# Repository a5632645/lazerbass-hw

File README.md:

# half demo  
watch it on https://www.bilibili.com/video/BV1h2w5eRECL

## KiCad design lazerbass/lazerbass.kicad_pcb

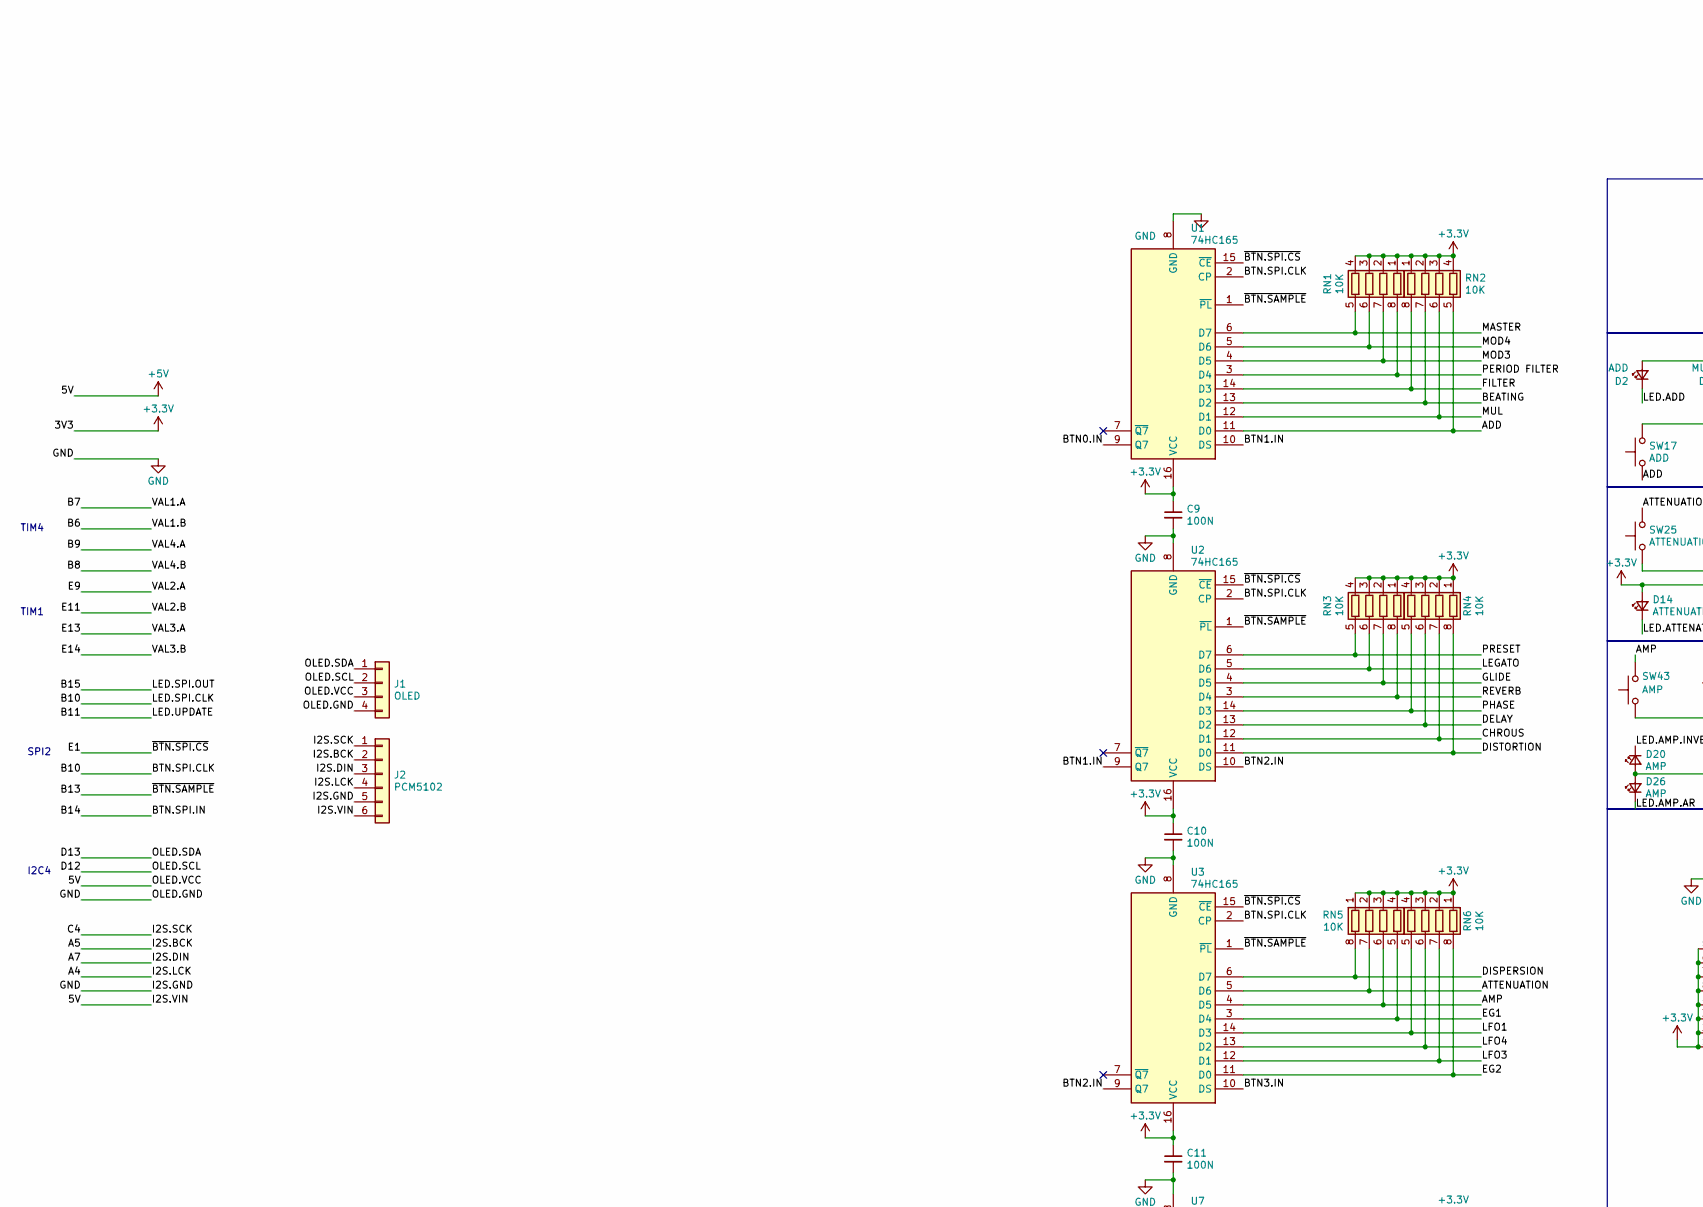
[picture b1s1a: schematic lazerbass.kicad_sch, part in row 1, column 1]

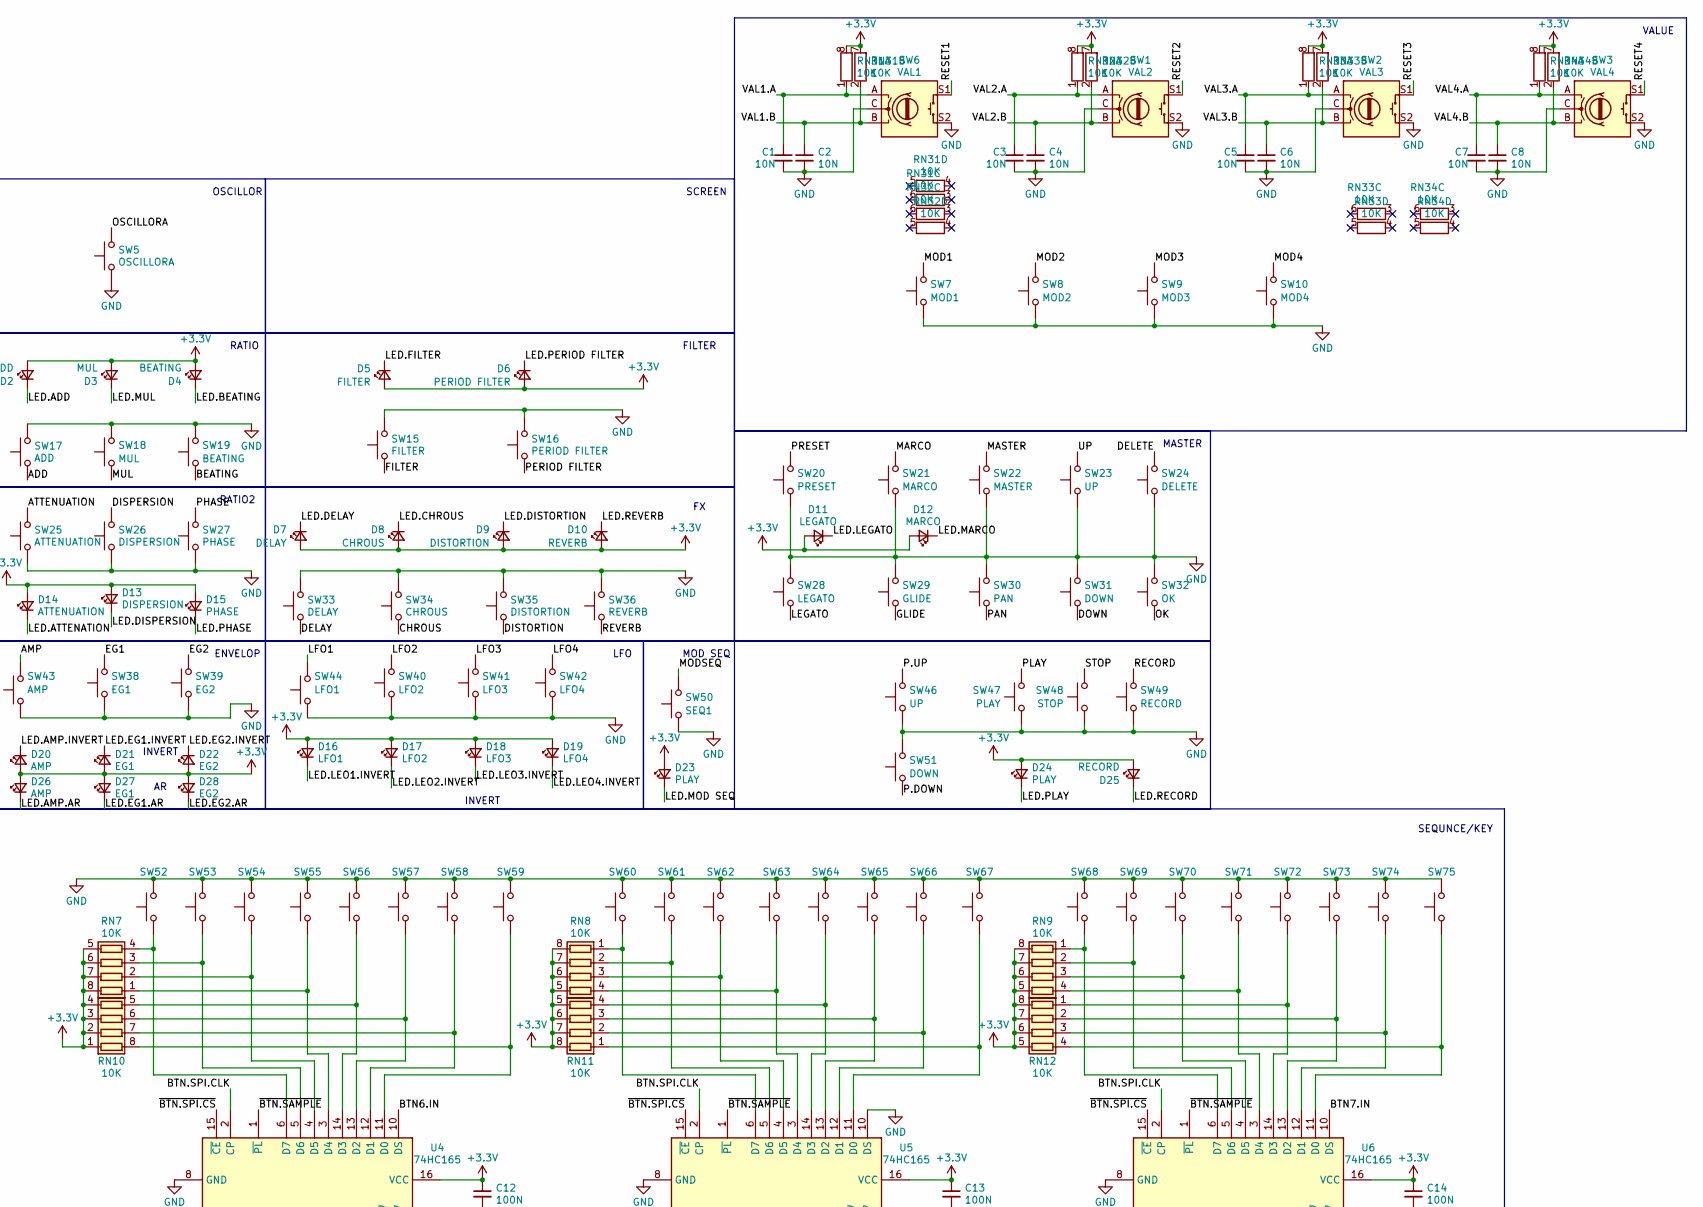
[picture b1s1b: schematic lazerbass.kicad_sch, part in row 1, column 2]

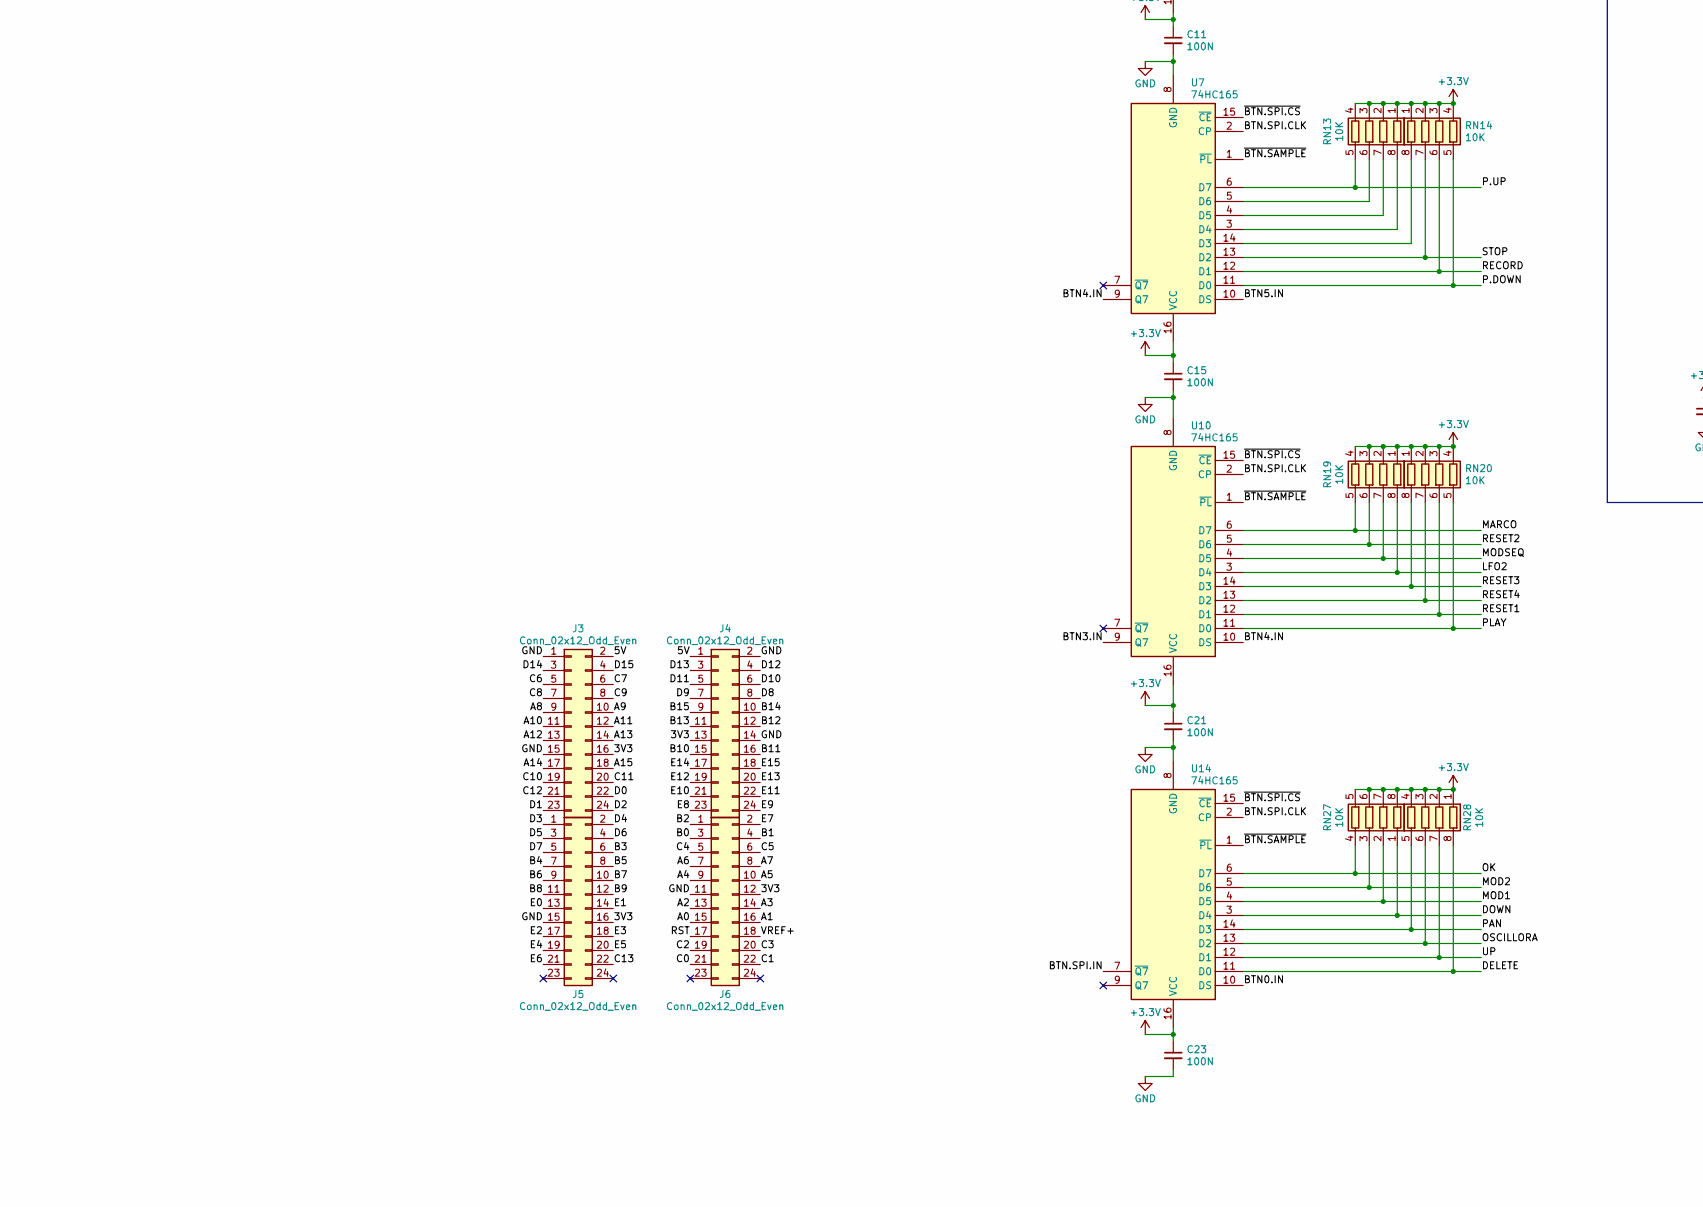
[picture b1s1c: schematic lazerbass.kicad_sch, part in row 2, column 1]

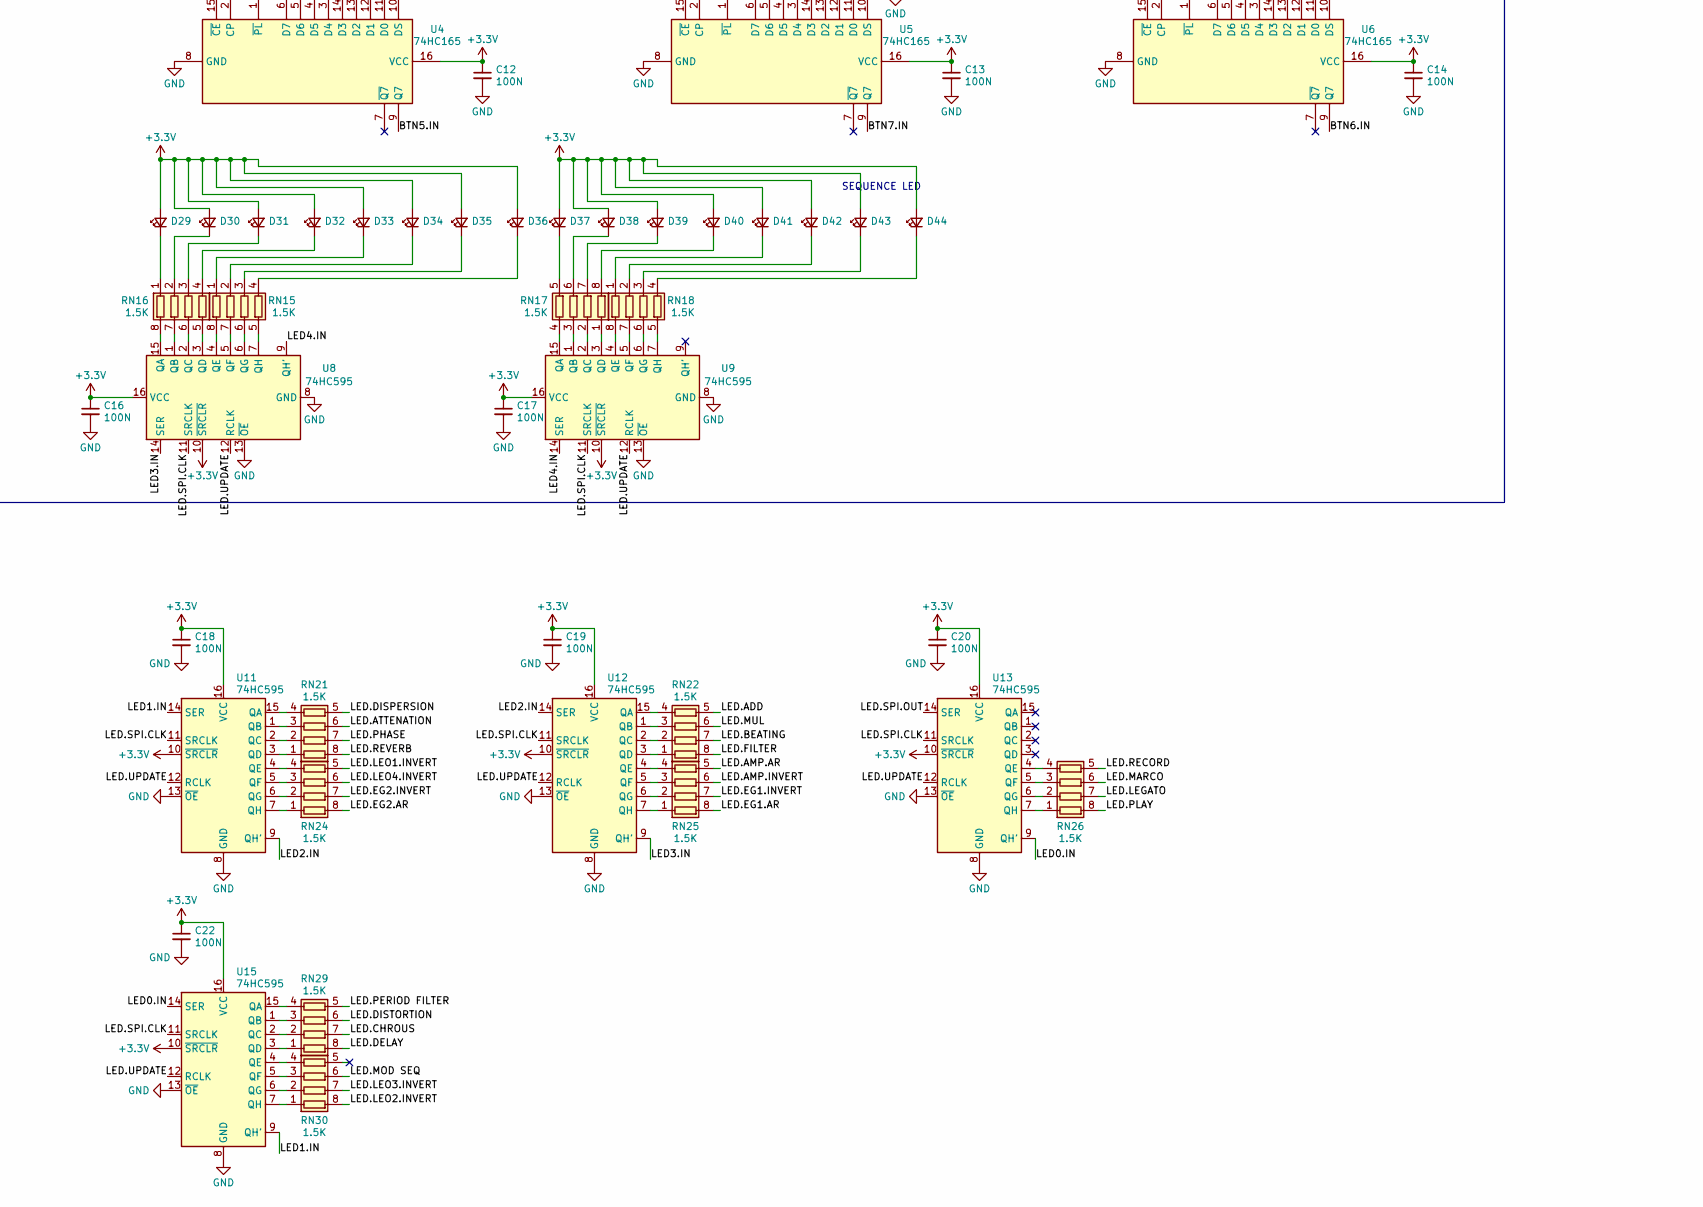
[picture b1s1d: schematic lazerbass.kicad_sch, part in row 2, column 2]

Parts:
C1, C2, C3, C4, C5, C6, C7, C8: 10N; C_0603_1608Metric
C9, C10, C11, C12, C13, C14, C15, C16, C17, C18, C19, C20, C21, C22, C23: 100N; C_0603_1608Metric
D2: ADD; LED_0805_2012Metric
D3: MUL; LED_0805_2012Metric
D4: BEATING; LED_0805_2012Metric
D5: FILTER; LED_0805_2012Metric
D6: PERIOD FILTER; LED_0805_2012Metric
D7: DELAY; LED_0805_2012Metric
D8: CHROUS; LED_0805_2012Metric
D9: DISTORTION; LED_0805_2012Metric
D10: REVERB; LED_0805_2012Metric
D11: LEGATO; LED_0805_2012Metric
D12: MARCO; LED_0805_2012Metric
D13: DISPERSION; LED_0805_2012Metric
D14: ATTENUATION; LED_0805_2012Metric
D15: PHASE; LED_0805_2012Metric
D16: LFO1; LED_0805_2012Metric
D17: LFO2; LED_0805_2012Metric
D18: LFO3; LED_0805_2012Metric
D19: LFO4; LED_0805_2012Metric
D20, D26: AMP; LED_0805_2012Metric
D21, D27: EG1; LED_0805_2012Metric
D22, D28: EG2; LED_0805_2012Metric
D23, D24: PLAY; LED_0805_2012Metric
D25: RECORD; LED_0805_2012Metric
D29, D30, D31, D32, D33, D34, D35, D36, D37, D38, D39, D40, D41, D42, D43, D44: LED_0805_2012Metric
J1: OLED; PinHeader_1x04_P2.54mm_Vertical
J2: PCM5102; PinHeader_1x06_P2.54mm_Vertical
J3, J4, J5, J6: Conn_02x12_Odd_Even; PinHeader_2x12_P2.54mm_Vertical_SMD
RN1, RN2, RN3, RN4, RN5, RN6, RN7, RN8, RN9, RN10, RN11, RN12, RN13, RN14, RN19, RN20, RN27, RN28: 10K; R_Array_Convex_4x0603
RN15, RN16, RN17, RN18, RN21, RN22, RN24, RN25, RN26, RN29, RN30: 1.5K; R_Array_Convex_4x0603
RN31, RN32, RN33, RN34: 10K; R_Array_Concave_4x0603
SW1: VAL2; SW-TH_EC11XXXXXXXX
SW2: VAL3; SW-TH_EC11XXXXXXXX
SW3: VAL4; SW-TH_EC11XXXXXXXX
SW5: OSCILLORA; SW-SMD_4P-L4.5-W4.5-P3.00-LS7.0_TS-1009S-03826; Mfg Part# 8-004 SMD Button 8x3.6mm Height=2.5mm
SW6: VAL1; SW-TH_EC11XXXXXXXX
SW7: MOD1; SW-SMD_4P-L4.5-W4.5-P3.00-LS7.0_TS-1009S-03826; Mfg Part# 8-004 SMD Button 8x3.6mm Height=2.5mm
SW8: MOD2; SW-SMD_4P-L4.5-W4.5-P3.00-LS7.0_TS-1009S-03826; Mfg Part# 8-004 SMD Button 8x3.6mm Height=2.5mm
SW9: MOD3; SW-SMD_4P-L4.5-W4.5-P3.00-LS7.0_TS-1009S-03826; Mfg Part# 8-004 SMD Button 8x3.6mm Height=2.5mm
SW10: MOD4; SW-SMD_4P-L4.5-W4.5-P3.00-LS7.0_TS-1009S-03826; Mfg Part# 8-004 SMD Button 8x3.6mm Height=2.5mm
SW15: FILTER; SW-SMD_4P-L4.5-W4.5-P3.00-LS7.0_TS-1009S-03826; Mfg Part# 8-004 SMD Button 8x3.6mm Height=2.5mm
SW16: PERIOD FILTER; SW-SMD_4P-L4.5-W4.5-P3.00-LS7.0_TS-1009S-03826; Mfg Part# 8-004 SMD Button 8x3.6mm Height=2.5mm
SW17: ADD; SW-SMD_4P-L4.5-W4.5-P3.00-LS7.0_TS-1009S-03826; Mfg Part# 8-004 SMD Button 8x3.6mm Height=2.5mm
SW18: MUL; SW-SMD_4P-L4.5-W4.5-P3.00-LS7.0_TS-1009S-03826; Mfg Part# 8-004 SMD Button 8x3.6mm Height=2.5mm
SW19: BEATING; SW-SMD_4P-L4.5-W4.5-P3.00-LS7.0_TS-1009S-03826; Mfg Part# 8-004 SMD Button 8x3.6mm Height=2.5mm
SW20: PRESET; SW-SMD_4P-L4.5-W4.5-P3.00-LS7.0_TS-1009S-03826; Mfg Part# 8-004 SMD Button 8x3.6mm Height=2.5mm
SW21: MARCO; SW-SMD_4P-L4.5-W4.5-P3.00-LS7.0_TS-1009S-03826; Mfg Part# 8-004 SMD Button 8x3.6mm Height=2.5mm
SW22: MASTER; SW-SMD_4P-L4.5-W4.5-P3.00-LS7.0_TS-1009S-03826; Mfg Part# 8-004 SMD Button 8x3.6mm Height=2.5mm
SW23, SW46: UP; SW-SMD_4P-L4.5-W4.5-P3.00-LS7.0_TS-1009S-03826; Mfg Part# 8-004 SMD Button 8x3.6mm Height=2.5mm
SW24: DELETE; SW-SMD_4P-L4.5-W4.5-P3.00-LS7.0_TS-1009S-03826; Mfg Part# 8-004 SMD Button 8x3.6mm Height=2.5mm
SW25: ATTENUATION; SW-SMD_4P-L4.5-W4.5-P3.00-LS7.0_TS-1009S-03826; Mfg Part# 8-004 SMD Button 8x3.6mm Height=2.5mm
SW26: DISPERSION; SW-SMD_4P-L4.5-W4.5-P3.00-LS7.0_TS-1009S-03826; Mfg Part# 8-004 SMD Button 8x3.6mm Height=2.5mm
SW27: PHASE; SW-SMD_4P-L4.5-W4.5-P3.00-LS7.0_TS-1009S-03826; Mfg Part# 8-004 SMD Button 8x3.6mm Height=2.5mm
SW28: LEGATO; SW-SMD_4P-L4.5-W4.5-P3.00-LS7.0_TS-1009S-03826; Mfg Part# 8-004 SMD Button 8x3.6mm Height=2.5mm
SW29: GLIDE; SW-SMD_4P-L4.5-W4.5-P3.00-LS7.0_TS-1009S-03826; Mfg Part# 8-004 SMD Button 8x3.6mm Height=2.5mm
SW30: PAN; SW-SMD_4P-L4.5-W4.5-P3.00-LS7.0_TS-1009S-03826; Mfg Part# 8-004 SMD Button 8x3.6mm Height=2.5mm
SW31, SW51: DOWN; SW-SMD_4P-L4.5-W4.5-P3.00-LS7.0_TS-1009S-03826; Mfg Part# 8-004 SMD Button 8x3.6mm Height=2.5mm
SW32: OK; SW-SMD_4P-L4.5-W4.5-P3.00-LS7.0_TS-1009S-03826; Mfg Part# 8-004 SMD Button 8x3.6mm Height=2.5mm
SW33: DELAY; SW-SMD_4P-L4.5-W4.5-P3.00-LS7.0_TS-1009S-03826; Mfg Part# 8-004 SMD Button 8x3.6mm Height=2.5mm
SW34: CHROUS; SW-SMD_4P-L4.5-W4.5-P3.00-LS7.0_TS-1009S-03826; Mfg Part# 8-004 SMD Button 8x3.6mm Height=2.5mm
SW35: DISTORTION; SW-SMD_4P-L4.5-W4.5-P3.00-LS7.0_TS-1009S-03826; Mfg Part# 8-004 SMD Button 8x3.6mm Height=2.5mm
SW36: REVERB; SW-SMD_4P-L4.5-W4.5-P3.00-LS7.0_TS-1009S-03826; Mfg Part# 8-004 SMD Button 8x3.6mm Height=2.5mm
SW38: EG1; SW-SMD_4P-L4.5-W4.5-P3.00-LS7.0_TS-1009S-03826; Mfg Part# 8-004 SMD Button 8x3.6mm Height=2.5mm
SW39: EG2; SW-SMD_4P-L4.5-W4.5-P3.00-LS7.0_TS-1009S-03826; Mfg Part# 8-004 SMD Button 8x3.6mm Height=2.5mm
SW40: LFO2; SW-SMD_4P-L4.5-W4.5-P3.00-LS7.0_TS-1009S-03826; Mfg Part# 8-004 SMD Button 8x3.6mm Height=2.5mm
SW41: LFO3; SW-SMD_4P-L4.5-W4.5-P3.00-LS7.0_TS-1009S-03826; Mfg Part# 8-004 SMD Button 8x3.6mm Height=2.5mm
SW42: LFO4; SW-SMD_4P-L4.5-W4.5-P3.00-LS7.0_TS-1009S-03826; Mfg Part# 8-004 SMD Button 8x3.6mm Height=2.5mm
SW43: AMP; SW-SMD_4P-L4.5-W4.5-P3.00-LS7.0_TS-1009S-03826; Mfg Part# 8-004 SMD Button 8x3.6mm Height=2.5mm
SW44: LFO1; SW-SMD_4P-L4.5-W4.5-P3.00-LS7.0_TS-1009S-03826; Mfg Part# 8-004 SMD Button 8x3.6mm Height=2.5mm
SW47: PLAY; SW-SMD_4P-L4.5-W4.5-P3.00-LS7.0_TS-1009S-03826; Mfg Part# 8-004 SMD Button 8x3.6mm Height=2.5mm
SW48: STOP; SW-SMD_4P-L4.5-W4.5-P3.00-LS7.0_TS-1009S-03826; Mfg Part# 8-004 SMD Button 8x3.6mm Height=2.5mm
SW49: RECORD; SW-SMD_4P-L4.5-W4.5-P3.00-LS7.0_TS-1009S-03826; Mfg Part# 8-004 SMD Button 8x3.6mm Height=2.5mm
SW50: SEQ1; SW-SMD_4P-L4.5-W4.5-P3.00-LS7.0_TS-1009S-03826; Mfg Part# 8-004 SMD Button 8x3.6mm Height=2.5mm
SW52, SW53, SW54, SW55, SW56, SW57, SW58, SW59, SW60, SW61, SW62, SW63, SW64, SW65, SW66, SW67, SW68, SW69, SW70, SW71, SW72, SW73, SW74, SW75: SMD_6x3.5mm_h2.5mm; SW-SMD_4P-L4.5-W4.5-P3.00-LS7.0_TS-1009S-03826; Mfg Part# 8-004 SMD Button 8x3.6mm Height=2.5mm
U1, U2, U3, U4, U5, U6, U7, U10, U14: 74HC165; SOIC-16_3.9x9.9mm_P1.27mm
U8, U9, U11, U12, U13, U15: 74HC595; SOIC-16_3.9x9.9mm_P1.27mm

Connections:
+3.3V: C9.1, C10.1, C11.1, C12.1, C13.1, C14.1, C15.1, C16.1, C17.1, C18.1, C19.1, C20.1, C21.1, C22.1, C23.1, D2.2 (A), D3.2 (A), D4.2 (A), D5.2 (A), D6.2 (A), D7.2 (A), D8.2 (A), D9.2 (A), D10.2 (A), D11.2 (A), D12.2 (A), D13.2 (A), D14.2 (A), D15.2 (A), D16.2 (A), D17.2 (A), D18.2 (A), D19.2 (A), D20.2 (A), D21.2 (A), D22.2 (A), D23.2 (A), D24.2 (A), D25.2 (A), D26.2 (A), D27.2 (A), D28.2 (A), D29.2 (A), D30.2 (A), D31.2 (A), D32.2 (A), D33.2 (A), D34.2 (A), D35.2 (A), D36.2 (A), D37.2 (A), D38.2 (A), D39.2 (A), D40.2 (A), D41.2 (A), D42.2 (A), D43.2 (A), D44.2 (A), J3.16, J4.13, J5.16, J6.12, RN1.1 (R1.1), RN1.2 (R2.1), RN1.3 (R3.1), RN1.4 (R4.1), RN2.1 (R1.1), RN2.2 (R2.1), RN2.3 (R3.1), RN2.4 (R4.1), RN3.1 (R1.1), RN3.2 (R2.1), RN3.3 (R3.1), RN3.4 (R4.1), RN4.1 (R1.1), RN4.2 (R2.1), RN4.3 (R3.1), RN4.4 (R4.1), RN5.1 (R1.1), RN5.2 (R2.1), RN5.3 (R3.1), RN5.4 (R4.1), RN6.1 (R1.1), RN6.2 (R2.1), RN6.3 (R3.1), RN6.4 (R4.1), RN7.5 (R4.2), RN7.6 (R3.2), RN7.7 (R2.2), RN7.8 (R1.2), RN8.5 (R4.2), RN8.6 (R3.2), RN8.7 (R2.2), RN8.8 (R1.2), RN9.5 (R4.2), RN9.6 (R3.2), RN9.7 (R2.2), RN9.8 (R1.2), RN10.1 (R1.1), RN10.2 (R2.1), RN10.3 (R3.1), RN10.4 (R4.1), RN11.5 (R4.2), RN11.6 (R3.2), RN11.7 (R2.2), RN11.8 (R1.2), RN12.5 (R4.2), RN12.6 (R3.2), RN12.7 (R2.2), RN12.8 (R1.2), RN13.1 (R1.1), RN13.2 (R2.1), RN13.3 (R3.1), RN13.4 (R4.1), RN14.1 (R1.1), RN14.2 (R2.1), RN14.3 (R3.1), RN14.4 (R4.1), RN19.1 (R1.1), RN19.2 (R2.1), RN19.3 (R3.1), RN19.4 (R4.1), RN20.1 (R1.1), RN20.2 (R2.1), RN20.3 (R3.1), RN20.4 (R4.1), RN27.5 (R4.2), RN27.6 (R3.2), RN27.7 (R2.2), RN27.8 (R1.2), RN28.1 (R1.1), RN28.2 (R2.1), RN28.3 (R3.1), RN28.4 (R4.1), RN31.7 (R2.2), RN31.8 (R1.2), RN32.7 (R2.2), RN32.8 (R1.2), RN33.7 (R2.2), RN33.8 (R1.2), RN34.7 (R2.2), RN34.8 (R1.2), U1.16 (VCC), U2.16 (VCC), U3.16 (VCC), U4.16 (VCC), U5.16 (VCC), U6.16 (VCC), U7.16 (VCC), U8.10 (~SRCLR), U8.16 (VCC), U9.10 (~SRCLR), U9.16 (VCC), U10.16 (VCC), U11.10 (~SRCLR), U11.16 (VCC), U12.10 (~SRCLR), U12.16 (VCC), U13.10 (~SRCLR), U13.16 (VCC), U14.16 (VCC), U15.10 (~SRCLR), U15.16 (VCC)
+5V: J1.3, J2.6, J3.2, J4.1
/A0: J6.15
/A1: J6.16
/A2: J6.13
/A3: J6.14
/A4: J2.4, J6.9
/A5: J2.2, J6.10
/A6: J6.7
/A7: J2.3, J6.8
/A8: J3.9
/A9: J3.10
/A10: J3.11
/A11: J3.12
/A12: J3.13
/A13: J3.14
/A14: J3.17
/A15: J3.18
/ADD: RN2.5 (R4.2), SW17.1, U1.11 (D0)
/AMP: RN5.6 (R3.2), SW43.2, U3.4 (D5)
/ATTENUATION: RN5.7 (R2.2), SW25.2, U3.5 (D6)
/B0: J6.3
/B1: J6.4
/B2: J6.1
/B3: J5.6
/B4: J5.7
/B5: J5.8
/B6: C2.1, J5.9, RN31.2 (R2.1), SW6.B
/B7: C1.1, J5.10, RN31.1 (R1.1), SW6.A
/B8: C8.1, J5.11, RN34.2 (R2.1), SW3.B
/B9: C7.1, J5.12, RN34.1 (R1.1), SW3.A
/B10: J4.15, U1.2 (CP), U2.2 (CP), U3.2 (CP), U4.2 (CP), U5.2 (CP), U6.2 (CP), U7.2 (CP), U8.11 (SRCLK), U9.11 (SRCLK), U10.2 (CP), U11.11 (SRCLK), U12.11 (SRCLK), U13.11 (SRCLK), U14.2 (CP), U15.11 (SRCLK)
/B11: J4.16, U8.12 (RCLK), U9.12 (RCLK), U11.12 (RCLK), U12.12 (RCLK), U13.12 (RCLK), U15.12 (RCLK)
/B12: J4.12
/B13: J4.11, U1.1 (~PL), U2.1 (~PL), U3.1 (~PL), U4.1 (~PL), U5.1 (~PL), U6.1 (~PL), U7.1 (~PL), U10.1 (~PL), U14.1 (~PL)
/B14: J4.10, U14.7 (~Q7)
/B15: J4.9, U13.14 (SER)
/BEATING: RN2.7 (R2.2), SW19.1, U1.13 (D2)
/BTN0.IN: U1.9 (Q7), U14.10 (DS)
/BTN1.IN: U1.10 (DS), U2.9 (Q7)
/BTN2.IN: U2.10 (DS), U3.9 (Q7)
/BTN3.IN: U3.10 (DS), U10.9 (Q7)
/BTN4.IN: U7.9 (Q7), U10.10 (DS)
/BTN5.IN: U4.9 (Q7), U7.10 (DS)
/BTN6.IN: U4.10 (DS), U6.9 (Q7)
/BTN7.IN: U5.9 (Q7), U6.10 (DS)
/C0: J6.21
/C1: J6.22
/C2: J6.19
/C3: J6.20
/C4: J2.1, J6.5
/C5: J6.6
/C6: J3.5
/C7: J3.6
/C8: J3.7
/C9: J3.8
/C10: J3.19
/C11: J3.20
/C12: J3.21
/C13: J5.22
/CHROUS: RN4.7 (R2.2), SW34.1, U2.12 (D1)
/D0: J3.22
/D1: J3.23
/D2: J3.24
/D3: J5.1
/D4: J5.2
/D5: J5.3
/D6: J5.4
/D7: J5.5
/D8: J4.8
/D9: J4.7
/D10: J4.6
/D11: J4.5
/D12: J1.2, J4.4
/D13: J1.1, J4.3
/D14: J3.3
/D15: J3.4
/DELAY: RN4.6 (R3.2), SW33.1, U2.13 (D2)
/DELETE: RN28.8 (R1.2), SW24.2, U14.11 (D0)
/DISPERSION: RN5.8 (R1.2), SW26.2, U3.6 (D7)
/DISTORTION: RN4.8 (R1.2), SW35.1, U2.11 (D0)
/DOWN: RN27.1 (R1.1), SW31.1, U14.3 (D4)
/E0: J5.13
/E1: J5.14, U1.15 (~CE), U2.15 (~CE), U3.15 (~CE), U4.15 (~CE), U5.15 (~CE), U6.15 (~CE), U7.15 (~CE), U10.15 (~CE), U14.15 (~CE)
/E2: J5.17
/E3: J5.18
/E4: J5.19
/E5: J5.20
/E6: J5.21
/E7: J6.2
/E8: J4.23
/E9: C3.1, J4.24, RN32.1 (R1.1), SW1.A
/E10: J4.21
/E11: C4.1, J4.22, RN32.2 (R2.1), SW1.B
/E12: J4.19
/E13: C5.1, J4.20, RN33.1 (R1.1), SW2.A
/E14: C6.1, J4.17, RN33.2 (R2.1), SW2.B
/E15: J4.18
/EG1: RN5.5 (R4.2), SW38.2, U3.3 (D4)
/EG2: RN6.8 (R1.2), SW39.2, U3.11 (D0)
/FILTER: RN2.8 (R1.2), SW15.1, U1.14 (D3)
/GLIDE: RN3.7 (R2.2), SW29.1, U2.4 (D5)
/LED0.IN: U13.9 (QH'), U15.14 (SER)
/LED1.IN: U11.14 (SER), U15.9 (QH')
/LED2.IN: U11.9 (QH'), U12.14 (SER)
/LED3.IN: U8.14 (SER), U12.9 (QH')
/LED4.IN: U8.9 (QH'), U9.14 (SER)
/LED.ADD: D2.1 (K), RN22.5 (R4.2)
/LED.AMP.AR: D26.1 (K), RN25.5 (R4.2)
/LED.AMP.INVERT: D20.1 (K), RN25.6 (R3.2)
/LED.ATTENATION: D14.1 (K), RN21.6 (R3.2)
/LED.BEATING: D4.1 (K), RN22.7 (R2.2)
/LED.CHROUS: D8.1 (K), RN29.7 (R2.2)
/LED.DELAY: D7.1 (K), RN29.8 (R1.2)
/LED.DISPERSION: D13.1 (K), RN21.5 (R4.2)
/LED.DISTORTION: D9.1 (K), RN29.6 (R3.2)
/LED.EG1.AR: D27.1 (K), RN25.8 (R1.2)
/LED.EG1.INVERT: D21.1 (K), RN25.7 (R2.2)
/LED.EG2.AR: D28.1 (K), RN24.8 (R1.2)
/LED.EG2.INVERT: D22.1 (K), RN24.7 (R2.2)
/LED.FILTER: D5.1 (K), RN22.8 (R1.2)
/LED.LEGATO: D11.1 (K), RN26.7 (R2.2)
/LED.LEO1.INVERT: D16.1 (K), RN24.5 (R4.2)
/LED.LEO2.INVERT: D17.1 (K), RN30.8 (R1.2)
/LED.LEO3.INVERT: D18.1 (K), RN30.7 (R2.2)
/LED.LEO4.INVERT: D19.1 (K), RN24.6 (R3.2)
/LED.MARCO: D12.1 (K), RN26.6 (R3.2)
/LED.MOD SEQ: D23.1 (K), RN30.6 (R3.2)
/LED.MUL: D3.1 (K), RN22.6 (R3.2)
/LED.PERIOD FILTER: D6.1 (K), RN29.5 (R4.2)
/LED.PHASE: D15.1 (K), RN21.7 (R2.2)
/LED.PLAY: D24.1 (K), RN26.8 (R1.2)
/LED.RECORD: D25.1 (K), RN26.5 (R4.2)
/LED.REVERB: D10.1 (K), RN21.8 (R1.2)
/LEGATO: RN3.6 (R3.2), SW28.1, U2.5 (D6)
/LFO1: RN6.5 (R4.2), SW44.2, U3.14 (D3)
/LFO2: RN19.8 (R1.2), SW40.2, U10.3 (D4)
/LFO3: RN6.7 (R2.2), SW41.2, U3.12 (D1)
/LFO4: RN6.6 (R3.2), SW42.2, U3.13 (D2)
/MARCO: RN19.5 (R4.2), SW21.2, U10.6 (D7)
/MASTER: RN1.5 (R4.2), SW22.2, U1.6 (D7)
/MOD1: RN27.2 (R2.1), SW7.2, U14.4 (D5)
/MOD2: RN27.3 (R3.1), SW8.2, U14.5 (D6)
/MOD3: RN1.7 (R2.2), SW9.2, U1.4 (D5)
/MOD4: RN1.6 (R3.2), SW10.2, U1.5 (D6)
/MODSEQ: RN19.7 (R2.2), SW50.2, U10.4 (D5)
/MUL: RN2.6 (R3.2), SW18.1, U1.12 (D1)
/OK: RN27.4 (R4.1), SW32.1, U14.6 (D7)
/OSCILLORA: RN28.6 (R3.2), SW5.2, U14.13 (D2)
/P.DOWN: RN14.5 (R4.2), SW51.1, U7.11 (D0)
/P.UP: RN13.5 (R4.2), SW46.2, U7.6 (D7)
/PAN: RN28.5 (R4.2), SW30.1, U14.14 (D3)
/PERIOD FILTER: RN1.8 (R1.2), SW16.1, U1.3 (D4)
/PHASE: RN4.5 (R4.2), SW27.2, U2.14 (D3)
/PLAY: RN20.5 (R4.2), SW47.2, U10.11 (D0)
/PRESET: RN3.5 (R4.2), SW20.2, U2.6 (D7)
/RECORD: RN14.6 (R3.2), SW49.2, U7.12 (D1)
/RESET1: RN20.6 (R3.2), SW6.S1, U10.12 (D1)
/RESET2: RN19.6 (R3.2), SW1.S1, U10.5 (D6)
/RESET3: RN20.8 (R1.2), SW2.S1, U10.14 (D3)
/RESET4: RN20.7 (R2.2), SW3.S1, U10.13 (D2)
/REVERB: RN3.8 (R1.2), SW36.1, U2.3 (D4)
/RST: J6.17
/STOP: RN14.7 (R2.2), SW48.2, U7.13 (D2)
/UP: RN28.7 (R2.2), SW23.2, U14.12 (D1)
/VREF+: J6.18
GND: C1.2, C2.2, C3.2, C4.2, C5.2, C6.2, C7.2, C8.2, C9.2, C10.2, C11.2, C12.2, C13.2, C14.2, C15.2, C16.2, C17.2, C18.2, C19.2, C20.2, C21.2, C22.2, C23.2, J1.4, J2.5, J3.1, J3.15, J4.2, J4.14, J5.15, J6.11, SW1.C, SW1.S2, SW2.C, SW2.S2, SW3.C, SW3.S2, SW5.1, SW6.C, SW6.S2, SW7.1, SW8.1, SW9.1, SW10.1, SW15.2, SW16.2, SW17.2, SW18.2, SW19.2, SW20.1, SW21.1, SW22.1, SW23.1, SW24.1, SW25.1, SW26.1, SW27.1, SW28.2, SW29.2, SW30.2, SW31.2, SW32.2, SW33.2, SW34.2, SW35.2, SW36.2, SW38.1, SW39.1, SW40.1, SW41.1, SW42.1, SW43.1, SW44.1, SW46.1, SW47.1, SW48.1, SW49.1, SW50.1, SW51.2, SW52.2, SW53.2, SW54.2, SW55.2, SW56.2, SW57.2, SW58.2, SW59.2, SW60.2, SW61.2, SW62.2, SW63.2, SW64.2, SW65.2, SW66.2, SW67.2, SW68.2, SW69.2, SW70.2, SW71.2, SW72.2, SW73.2, SW74.2, SW75.2, U1.8 (GND), U2.8 (GND), U3.8 (GND), U4.8 (GND), U5.8 (GND), U5.10 (DS), U6.8 (GND), U7.8 (GND), U8.8 (GND), U8.13 (~OE), U9.8 (GND), U9.13 (~OE), U10.8 (GND), U11.8 (GND), U11.13 (~OE), U12.8 (GND), U12.13 (~OE), U13.8 (GND), U13.13 (~OE), U14.8 (GND), U15.8 (GND), U15.13 (~OE)
unnamed: D29.1 (K), RN16.1 (R1.1)
unnamed: D30.1 (K), RN16.2 (R2.1)
unnamed: D31.1 (K), RN16.3 (R3.1)
unnamed: D32.1 (K), RN16.4 (R4.1)
unnamed: D33.1 (K), RN15.1 (R1.1)
unnamed: D34.1 (K), RN15.2 (R2.1)
unnamed: D35.1 (K), RN15.3 (R3.1)
unnamed: D36.1 (K), RN15.4 (R4.1)
unnamed: D37.1 (K), RN17.5 (R4.2)
unnamed: D38.1 (K), RN17.6 (R3.2)
unnamed: D39.1 (K), RN17.7 (R2.2)
unnamed: D40.1 (K), RN17.8 (R1.2)
unnamed: D41.1 (K), RN18.1 (R1.1)
unnamed: D42.1 (K), RN18.2 (R2.1)
unnamed: D43.1 (K), RN18.3 (R3.1)
unnamed: D44.1 (K), RN18.4 (R4.1)
unnamed: RN7.1 (R1.1), SW55.1, U4.3 (D4)
unnamed: RN7.2 (R2.1), SW54.1, U4.4 (D5)
unnamed: RN7.3 (R3.1), SW53.1, U4.5 (D6)
unnamed: RN7.4 (R4.1), SW52.1, U4.6 (D7)
unnamed: RN8.1 (R1.1), SW60.1, U5.6 (D7)
unnamed: RN8.2 (R2.1), SW61.1, U5.5 (D6)
unnamed: RN8.3 (R3.1), SW62.1, U5.4 (D5)
unnamed: RN8.4 (R4.1), SW63.1, U5.3 (D4)
unnamed: RN9.1 (R1.1), SW68.1, U6.6 (D7)
unnamed: RN9.2 (R2.1), SW69.1, U6.5 (D6)
unnamed: RN9.3 (R3.1), SW70.1, U6.4 (D5)
unnamed: RN9.4 (R4.1), SW71.1, U6.3 (D4)
unnamed: RN10.8 (R1.2), SW59.1, U4.11 (D0)
unnamed: RN10.7 (R2.2), SW58.1, U4.12 (D1)
unnamed: RN10.6 (R3.2), SW57.1, U4.13 (D2)
unnamed: RN10.5 (R4.2), SW56.1, U4.14 (D3)
unnamed: RN11.1 (R1.1), SW67.1, U5.11 (D0)
unnamed: RN11.2 (R2.1), SW66.1, U5.12 (D1)
unnamed: RN11.3 (R3.1), SW65.1, U5.13 (D2)
unnamed: RN11.4 (R4.1), SW64.1, U5.14 (D3)
unnamed: RN12.1 (R1.1), SW72.1, U6.14 (D3)
unnamed: RN12.2 (R2.1), SW73.1, U6.13 (D2)
unnamed: RN12.3 (R3.1), SW74.1, U6.12 (D1)
unnamed: RN12.4 (R4.1), SW75.1, U6.11 (D0)
unnamed: RN15.8 (R1.2), U8.4 (QE)
unnamed: RN15.7 (R2.2), U8.5 (QF)
unnamed: RN15.6 (R3.2), U8.6 (QG)
unnamed: RN15.5 (R4.2), U8.7 (QH)
unnamed: RN16.8 (R1.2), U8.15 (QA)
unnamed: RN16.7 (R2.2), U8.1 (QB)
unnamed: RN16.6 (R3.2), U8.2 (QC)
unnamed: RN16.5 (R4.2), U8.3 (QD)
unnamed: RN17.1 (R1.1), U9.3 (QD)
unnamed: RN17.2 (R2.1), U9.2 (QC)
unnamed: RN17.3 (R3.1), U9.1 (QB)
unnamed: RN17.4 (R4.1), U9.15 (QA)
unnamed: RN18.8 (R1.2), U9.4 (QE)
unnamed: RN18.7 (R2.2), U9.5 (QF)
unnamed: RN18.6 (R3.2), U9.6 (QG)
unnamed: RN18.5 (R4.2), U9.7 (QH)
unnamed: RN21.1 (R1.1), U11.3 (QD)
unnamed: RN21.2 (R2.1), U11.2 (QC)
unnamed: RN21.3 (R3.1), U11.1 (QB)
unnamed: RN21.4 (R4.1), U11.15 (QA)
unnamed: RN22.1 (R1.1), U12.3 (QD)
unnamed: RN22.2 (R2.1), U12.2 (QC)
unnamed: RN22.3 (R3.1), U12.1 (QB)
unnamed: RN22.4 (R4.1), U12.15 (QA)
unnamed 231: U13.3 (QD); also elsewhere on the board
unnamed 232: U13.2 (QC); also elsewhere on the board
unnamed 233: U13.1 (QB); also elsewhere on the board
unnamed 234: U13.15 (QA); also elsewhere on the board
unnamed: RN24.1 (R1.1), U11.7 (QH)
unnamed: RN24.2 (R2.1), U11.6 (QG)
unnamed: RN24.3 (R3.1), U11.5 (QF)
unnamed: RN24.4 (R4.1), U11.4 (QE)
unnamed: RN25.1 (R1.1), U12.7 (QH)
unnamed: RN25.2 (R2.1), U12.6 (QG)
unnamed: RN25.3 (R3.1), U12.5 (QF)
unnamed: RN25.4 (R4.1), U12.4 (QE)
unnamed: RN26.1 (R1.1), U13.7 (QH)
unnamed: RN26.2 (R2.1), U13.6 (QG)
unnamed: RN26.3 (R3.1), U13.5 (QF)
unnamed: RN26.4 (R4.1), U13.4 (QE)
unnamed: RN29.1 (R1.1), U15.3 (QD)
unnamed: RN29.2 (R2.1), U15.2 (QC)
unnamed: RN29.3 (R3.1), U15.1 (QB)
unnamed: RN29.4 (R4.1), U15.15 (QA)
unnamed: RN30.1 (R1.1), U15.7 (QH)
unnamed: RN30.2 (R2.1), U15.6 (QG)
unnamed: RN30.3 (R3.1), U15.5 (QF)
unnamed: RN30.4 (R4.1), U15.4 (QE)

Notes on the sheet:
TIM4
INVERT
OSCILLOR
VALUE
TIM1
SEQUENCE LED
LFO
SPI2
SCREEN
I2C4
FILTER
RATIO
MOD SEQ
ENVELOP
SEQUNCE/KEY
RATIO2
MASTER

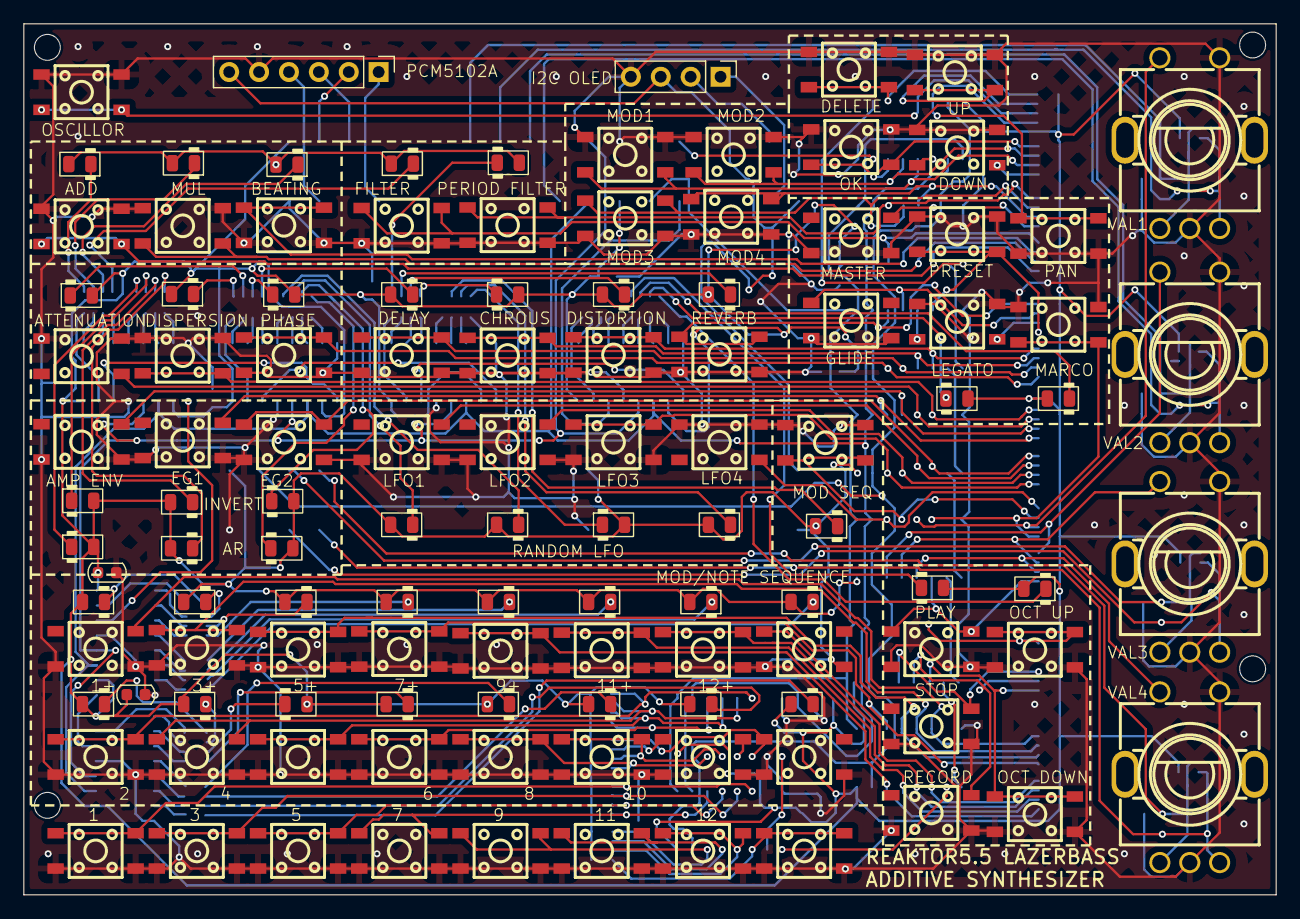
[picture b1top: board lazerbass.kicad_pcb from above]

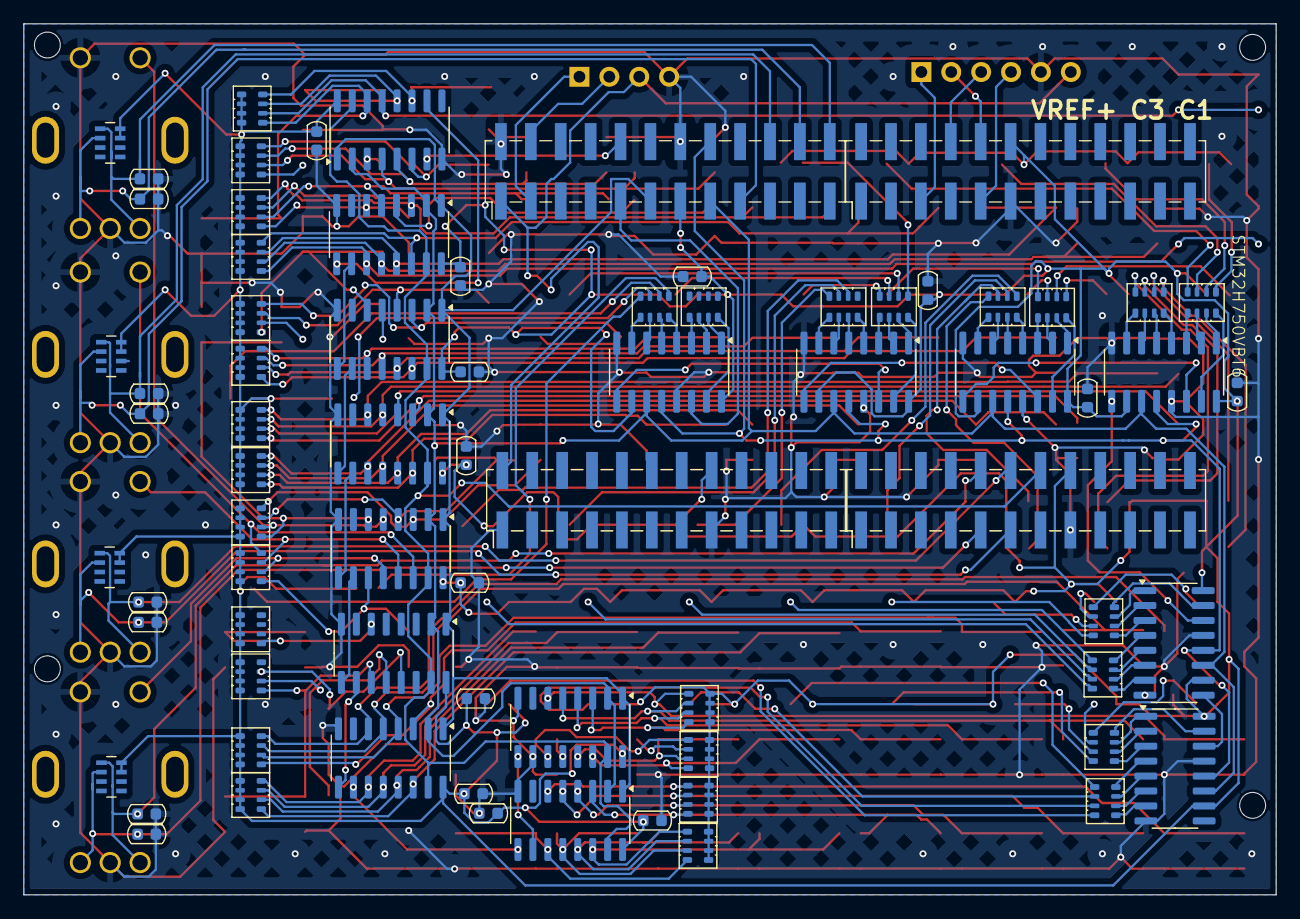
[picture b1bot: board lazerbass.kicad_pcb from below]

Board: 2 copper layers, 106.4 x 74.0 mm, 189 parts (74 on the bottom side), 195 nets.

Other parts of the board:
RN23: 1.5K; R_Array_Convex_4x0603

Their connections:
unnamed 231: RN23.1 (R1.1); also elsewhere on the board
unnamed 232: RN23.2 (R2.1); also elsewhere on the board
unnamed 233: RN23.3 (R3.1); also elsewhere on the board
unnamed 234: RN23.4 (R4.1); also elsewhere on the board

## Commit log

2025-06-30 init
